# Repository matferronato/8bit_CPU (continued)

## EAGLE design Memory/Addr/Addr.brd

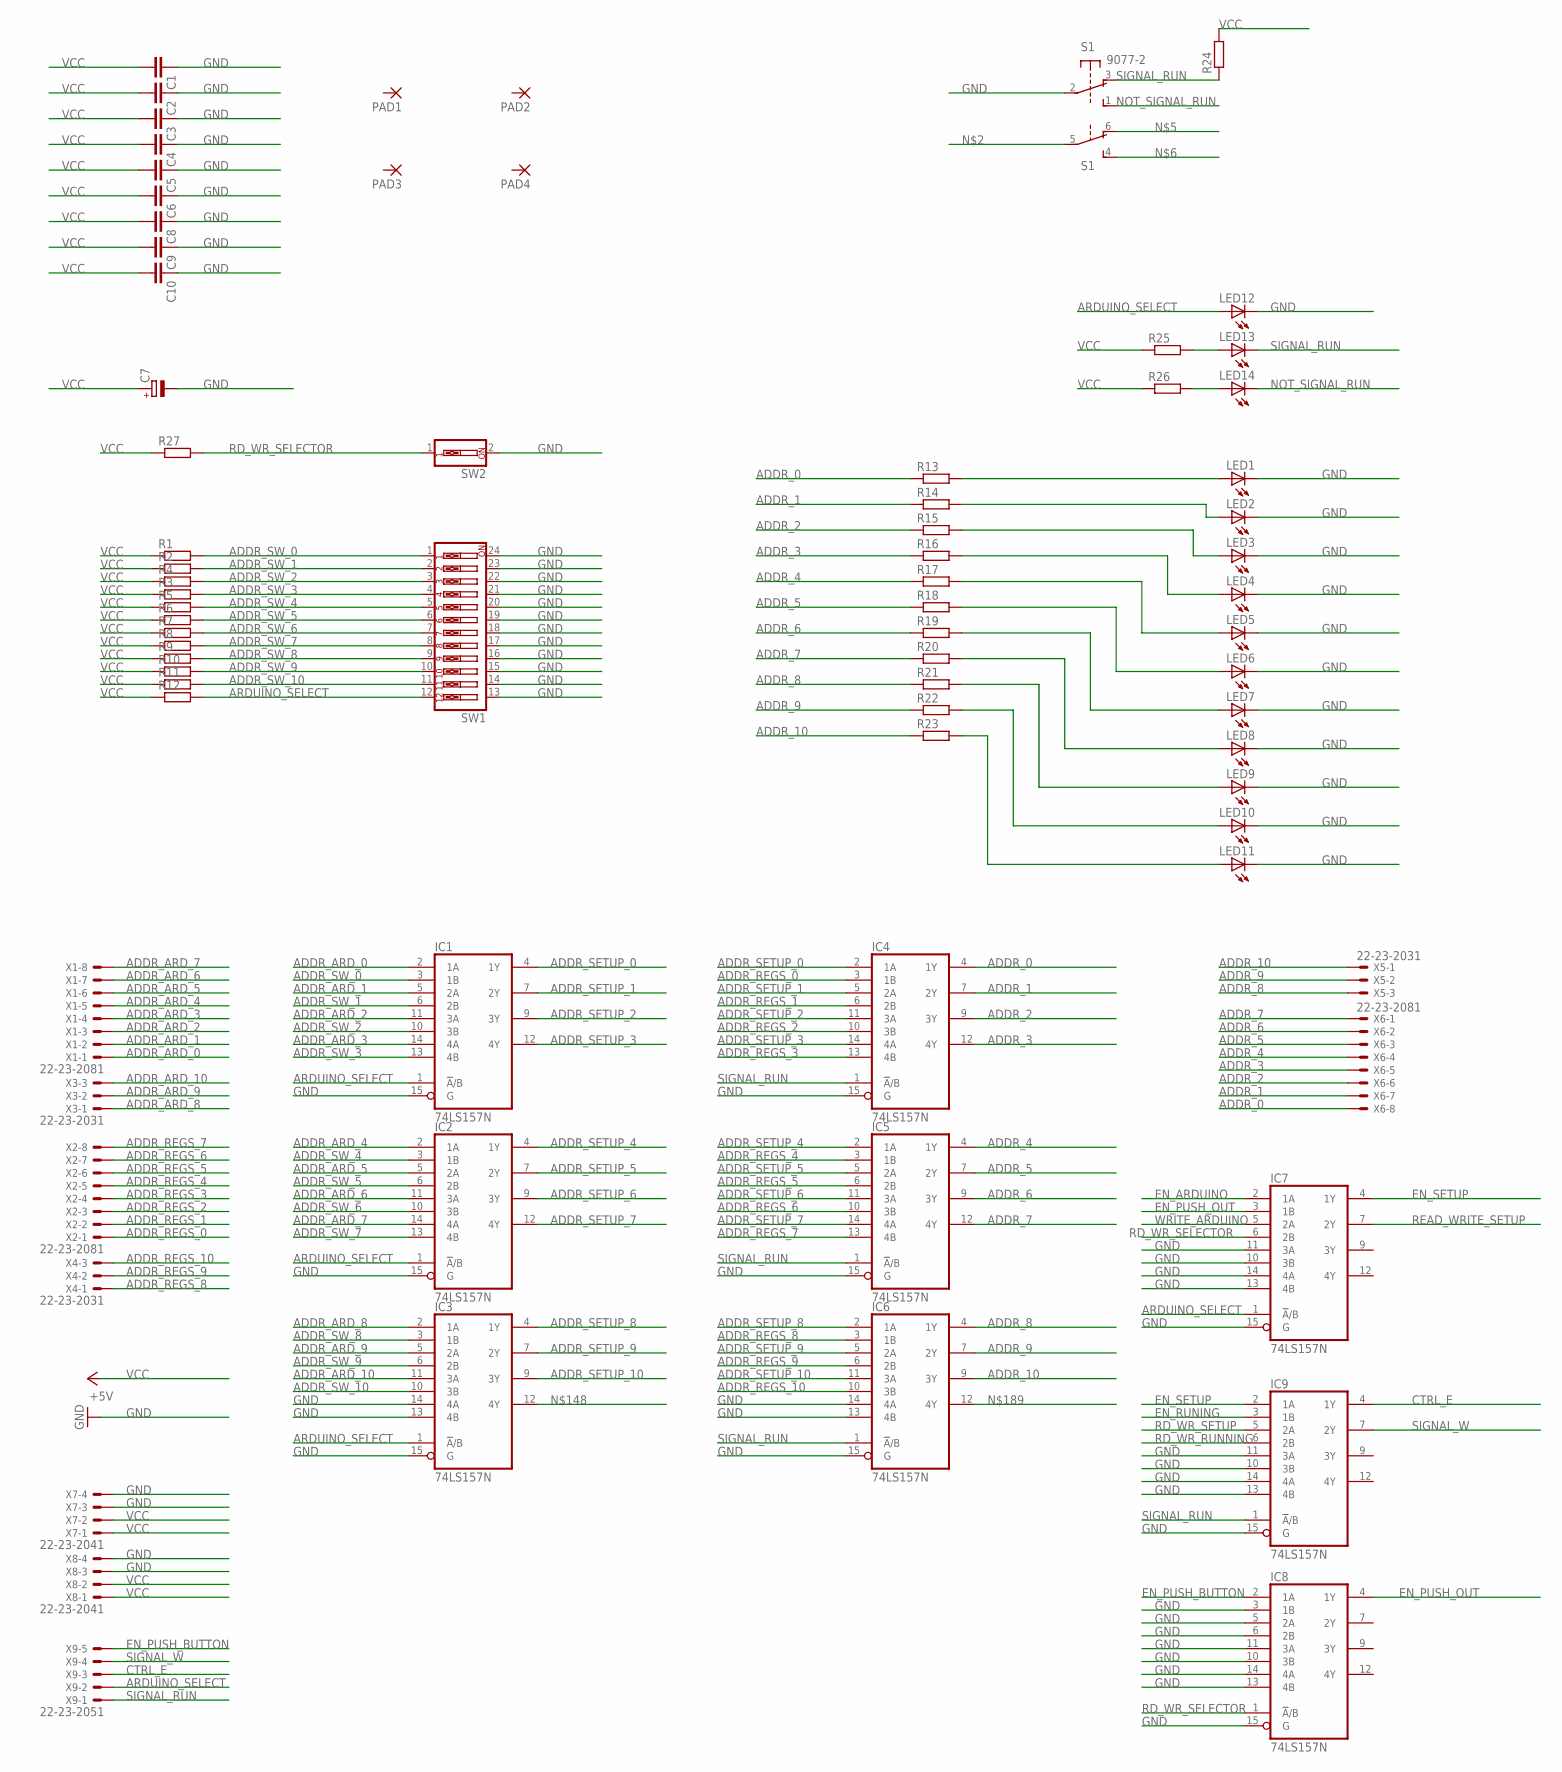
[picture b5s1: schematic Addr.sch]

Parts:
C1, C2, C3, C4, C5, C6, C8, C9, C10: C-EU025-025X050; C025-025X050
C7: CPOL-EUE2.5-6; E2,5-6
IC1, IC2, IC3, IC4, IC5, IC6, IC7, IC8, IC9: 74LS157N; DIL16
LED1, LED2, LED3, LED4, LED5, LED6, LED7, LED8, LED9, LED10, LED11, LED12, LED13, LED14: LED5MM
PAD1, PAD2, PAD3, PAD4: 3,17/1,3
R1, R2, R3, R4, R5, R6, R7, R8, R9, R10, R11, R12, R13, R14, R15, R16, R17, R18, R19, R20, R21, R22, R23, R24, R25, R26, R27: R0207/10; 0207/10
S1: 9077-2
SW1: SW_DIP-12; EDG-12
SW2: SW_DIP-1; EDG-01
X1, X2, X6: 22-23-2081
X3, X4, X5: 22-23-2031
X7, X8: 22-23-2041
X9: 22-23-2051

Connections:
ADDR_0: IC4.4 (1Y), R13.1, X6.8
ADDR_1: IC4.7 (2Y), R14.1, X6.7
ADDR_2: IC4.9 (3Y), R15.1, X6.6
ADDR_3: IC4.12 (4Y), R16.1, X6.5
ADDR_4: IC5.4 (1Y), R17.1, X6.4
ADDR_5: IC5.7 (2Y), R18.1, X6.3
ADDR_6: IC5.9 (3Y), R19.1, X6.2
ADDR_7: IC5.12 (4Y), R20.1, X6.1
ADDR_8: IC6.4 (1Y), R21.1, X5.3
ADDR_9: IC6.7 (2Y), R22.1, X5.2
ADDR_10: IC6.9 (3Y), R23.1, X5.1
ADDR_ARD_0: IC1.2 (1A), X1.1
ADDR_ARD_1: IC1.5 (2A), X1.2
ADDR_ARD_2: IC1.11 (3A), X1.3
ADDR_ARD_3: IC1.14 (4A), X1.4
ADDR_ARD_4: IC2.2 (1A), X1.5
ADDR_ARD_5: IC2.5 (2A), X1.6
ADDR_ARD_6: IC2.11 (3A), X1.7
ADDR_ARD_7: IC2.14 (4A), X1.8
ADDR_ARD_8: IC3.2 (1A), X3.1
ADDR_ARD_9: IC3.5 (2A), X3.2
ADDR_ARD_10: IC3.11 (3A), X3.3
ADDR_REGS_0: IC4.3 (1B), X2.1
ADDR_REGS_1: IC4.6 (2B), X2.2
ADDR_REGS_2: IC4.10 (3B), X2.3
ADDR_REGS_3: IC4.13 (4B), X2.4
ADDR_REGS_4: IC5.3 (1B), X2.5
ADDR_REGS_5: IC5.6 (2B), X2.6
ADDR_REGS_6: IC5.10 (3B), X2.7
ADDR_REGS_7: IC5.13 (4B), X2.8
ADDR_REGS_8: IC6.3 (1B), X4.1
ADDR_REGS_9: IC6.6 (2B), X4.2
ADDR_REGS_10: IC6.10 (3B), X4.3
ADDR_SETUP_0: IC1.4 (1Y), IC4.2 (1A)
ADDR_SETUP_1: IC1.7 (2Y), IC4.5 (2A)
ADDR_SETUP_2: IC1.9 (3Y), IC4.11 (3A)
ADDR_SETUP_3: IC1.12 (4Y), IC4.14 (4A)
ADDR_SETUP_4: IC2.4 (1Y), IC5.2 (1A)
ADDR_SETUP_5: IC2.7 (2Y), IC5.5 (2A)
ADDR_SETUP_6: IC2.9 (3Y), IC5.11 (3A)
ADDR_SETUP_7: IC2.12 (4Y), IC5.14 (4A)
ADDR_SETUP_8: IC3.4 (1Y), IC6.2 (1A)
ADDR_SETUP_9: IC3.7 (2Y), IC6.5 (2A)
ADDR_SETUP_10: IC3.9 (3Y), IC6.11 (3A)
ADDR_SW_0: IC1.3 (1B), R1.2, SW1.1
ADDR_SW_1: IC1.6 (2B), R2.2, SW1.2
ADDR_SW_2: IC1.10 (3B), R4.2, SW1.3
ADDR_SW_3: IC1.13 (4B), R3.2, SW1.4
ADDR_SW_4: IC2.3 (1B), R5.2, SW1.5
ADDR_SW_5: IC2.6 (2B), R6.2, SW1.6
ADDR_SW_6: IC2.10 (3B), R7.2, SW1.7
ADDR_SW_7: IC2.13 (4B), R8.2, SW1.8
ADDR_SW_8: IC3.3 (1B), R9.2, SW1.9
ADDR_SW_9: IC3.6 (2B), R10.2, SW1.10
ADDR_SW_10: IC3.10 (3B), R11.2, SW1.11
ARDUINO_SELECT: IC1.1 (!A!/B), IC2.1 (!A!/B), IC3.1 (!A!/B), IC7.1 (!A!/B), LED12.A, R12.2, SW1.12, X9.2
CTRL_E: IC9.4 (1Y), X9.3
EN_ARDUINO: IC7.2 (1A)
EN_PUSH_BUTTON: IC8.2 (1A), X9.5
EN_PUSH_OUT: IC7.3 (1B), IC8.4 (1Y)
EN_RUNING: IC9.3 (1B)
EN_SETUP: IC7.4 (1Y), IC9.2 (1A)
GND: C1.1, C2.1, C3.1, C4.1, C5.1, C6.1, C7.-, C8.1, C9.1, C10.1, IC1.8 (GND), IC1.15 (G), IC2.8 (GND), IC2.15 (G), IC3.8 (GND), IC3.13 (4B), IC3.14 (4A), IC3.15 (G), IC4.8 (GND), IC4.15 (G), IC5.8 (GND), IC5.15 (G), IC6.8 (GND), IC6.13 (4B), IC6.14 (4A), IC6.15 (G), IC7.8 (GND), IC7.10 (3B), IC7.11 (3A), IC7.13 (4B), IC7.14 (4A), IC7.15 (G), IC8.3 (1B), IC8.5 (2A), IC8.6 (2B), IC8.8 (GND), IC8.10 (3B), IC8.11 (3A), IC8.13 (4B), IC8.14 (4A), IC8.15 (G), IC9.8 (GND), IC9.10 (3B), IC9.11 (3A), IC9.13 (4B), IC9.14 (4A), IC9.15 (G), LED1.K (C), LED2.K (C), LED3.K (C), LED4.K (C), LED5.K (C), LED6.K (C), LED7.K (C), LED8.K (C), LED9.K (C), LED10.K (C), LED11.K (C), LED12.K (C), S1.2, SW1.13, SW1.14, SW1.15, SW1.16, SW1.17, SW1.18, SW1.19, SW1.20, SW1.21, SW1.22, SW1.23, SW1.24, SW2.2, X7.3, X7.4, X8.3, X8.4
unnamed: LED13.A, R25.2
unnamed: LED14.A, R26.2
unnamed: LED1.A, R13.2
unnamed: LED2.A, R14.2
unnamed: LED3.A, R15.2
unnamed: LED4.A, R16.2
unnamed: LED5.A, R17.2
unnamed: LED6.A, R18.2
unnamed: LED7.A, R19.2
unnamed: LED8.A, R20.2
unnamed: LED9.A, R21.2
unnamed: LED10.A, R22.2
unnamed: LED11.A, R23.2
NOT_SIGNAL_RUN: LED14.K (C), S1.1 (S)
RD_WR_RUNNING: IC9.6 (2B)
RD_WR_SELECTOR: IC7.6 (2B), IC8.1 (!A!/B), R27.2, SW2.1
RD_WR_SETUP: IC9.5 (2A)
READ_WRITE_SETUP: IC7.7 (2Y)
SIGNAL_RUN: IC4.1 (!A!/B), IC5.1 (!A!/B), IC6.1 (!A!/B), IC9.1 (!A!/B), LED13.K (C), R24.1, S1.3 (O), X9.1
SIGNAL_W: IC9.7 (2Y), X9.4
VCC: C1.2, C2.2, C3.2, C4.2, C5.2, C6.2, C7.+, C8.2, C9.2, C10.2, IC1.16 (VCC), IC2.16 (VCC), IC3.16 (VCC), IC4.16 (VCC), IC5.16 (VCC), IC6.16 (VCC), IC7.16 (VCC), IC8.16 (VCC), IC9.16 (VCC), R1.1, R2.1, R3.1, R4.1, R5.1, R6.1, R7.1, R8.1, R9.1, R10.1, R11.1, R12.1, R24.2, R25.1, R26.1, R27.1, X7.1, X7.2, X8.1, X8.2
WRITE_ARDUINO: IC7.5 (2A)

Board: 2 copper layers, 76 parts (0 on the bottom side), 79 nets, no tracks yet.

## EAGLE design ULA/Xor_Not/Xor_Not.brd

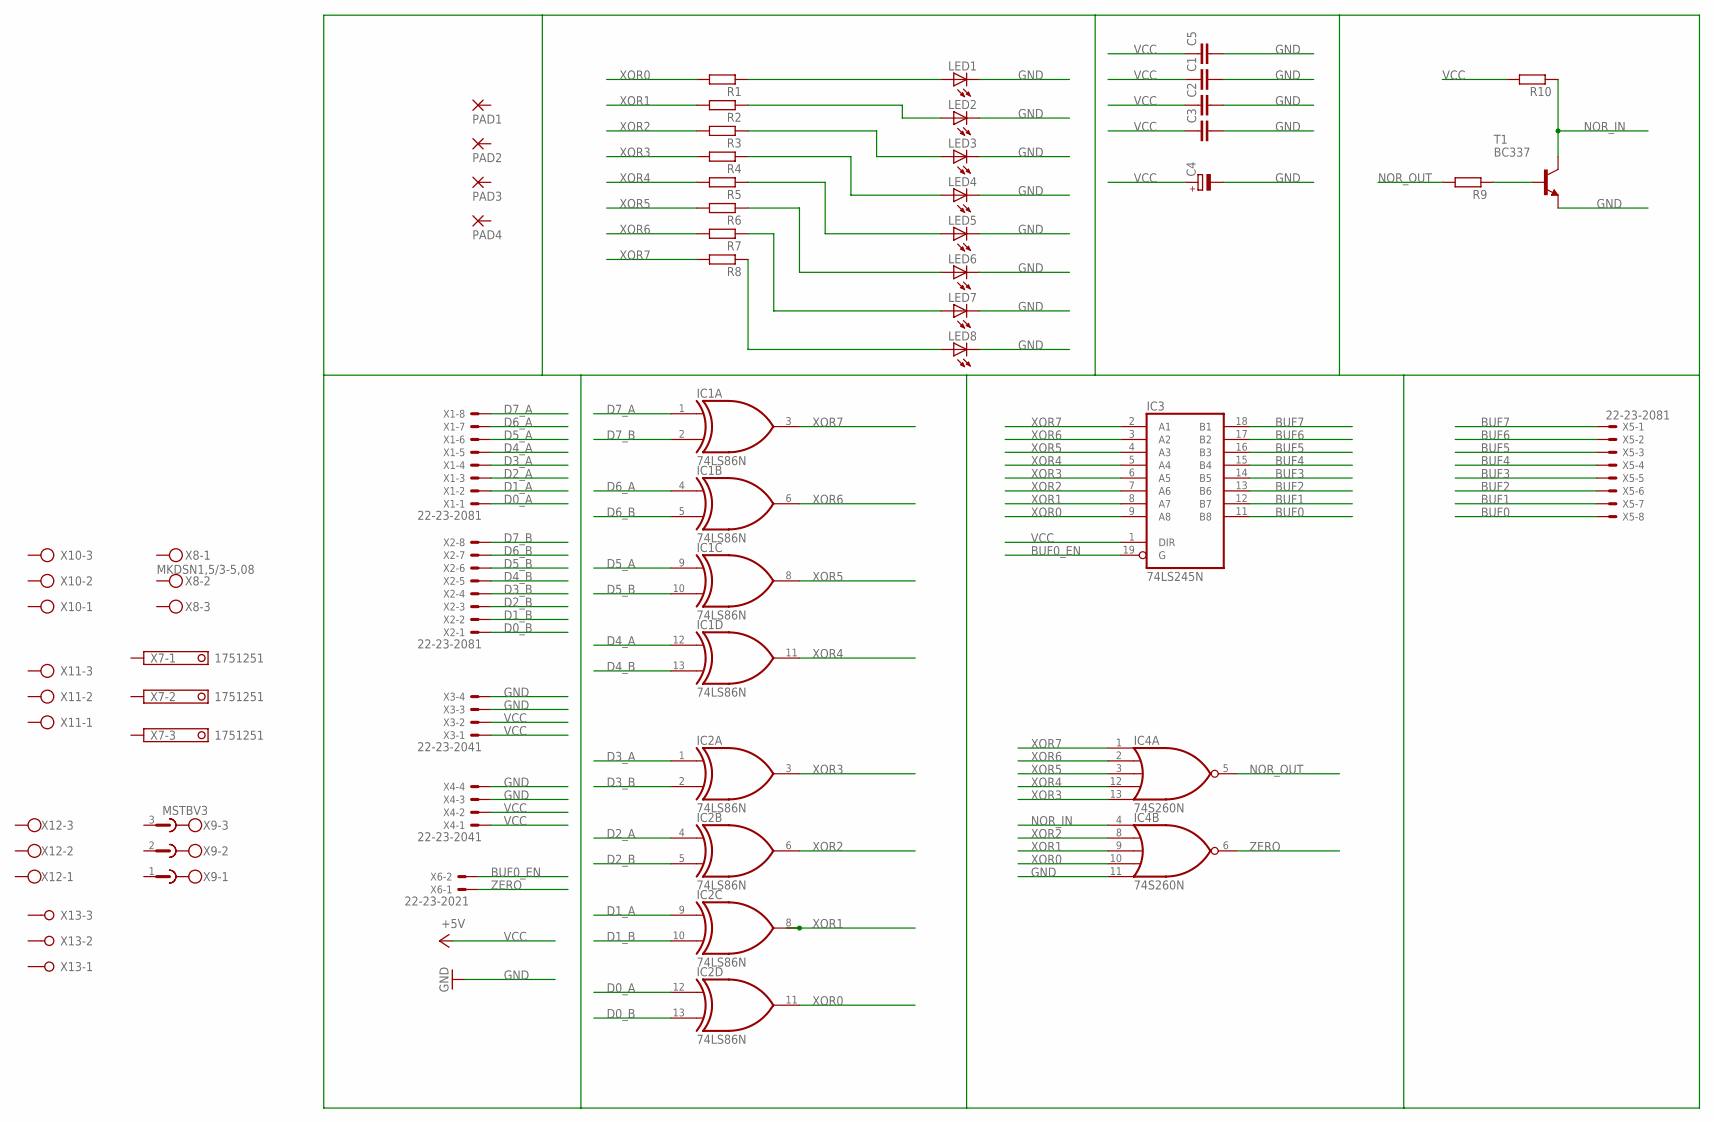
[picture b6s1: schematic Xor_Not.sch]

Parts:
C1, C2, C3, C5: C-EU025-025X050; C025-025X050
C4: CPOL-EUE2.5-6; E2,5-6
IC1, IC2: 74LS86N; DIL14
IC3: 74LS245N; DIL20
IC4: 74S260N; DIL14
LED1, LED2, LED3, LED4, LED5, LED6, LED7, LED8: LED5MM
PAD1, PAD2, PAD3, PAD4: 3,17/1,3
R1, R2, R3, R4, R5, R6, R7, R8, R9, R10: R0207/10; 0207/10
T1: BC337; TO92
X1, X2, X5: 22-23-2081
X3, X4: 22-23-2041
X6: 22-23-2021
X7: 1751251
X8: MKDSN1,5/3-5,08
X9: MSTBV3
X10: AK300/3
X11: AK500/3-H
X12: W237-103
X13: W237-03P; W237-133

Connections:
BUF0: IC3.11 (B8), X5.8
BUF0_EN: IC3.19 (G), X6.2
BUF1: IC3.12 (B7), X5.7
BUF2: IC3.13 (B6), X5.6
BUF3: IC3.14 (B5), X5.5
BUF4: IC3.15 (B4), X5.4
BUF5: IC3.16 (B3), X5.3
BUF6: IC3.17 (B2), X5.2
BUF7: IC3.18 (B1), X5.1
D0_A: IC2.12 (I0), X1.1
D0_B: IC2.13 (I1), X2.1
D1_A: IC2.9 (I0), X1.2
D1_B: IC2.10 (I1), X2.2
D2_A: IC2.4 (I0), X1.3
D2_B: IC2.5 (I1), X2.3
D3_A: IC2.1 (I0), X1.4
D3_B: IC2.2 (I1), X2.4
D4_A: IC1.12 (I0), X1.5
D4_B: IC1.13 (I1), X2.5
D5_A: IC1.9 (I0), X1.6
D5_B: IC1.10 (I1), X2.6
D6_A: IC1.4 (I0), X1.7
D6_B: IC1.5 (I1), X2.7
D7_A: IC1.1 (I0), X1.8
D7_B: IC1.2 (I1), X2.8
GND: C1.2, C2.2, C3.2, C4.-, C5.2, IC1.7 (GND), IC2.7 (GND), IC3.10 (GND), IC4.7 (GND), IC4.11 (I4), LED1.K (C), LED2.K (C), LED3.K (C), LED4.K (C), LED5.K (C), LED6.K (C), LED7.K (C), LED8.K (C), T1.1 (E), X3.3, X3.4, X4.3, X4.4
unnamed: R9.1, T1.2 (B)
unnamed: LED1.A, R1.1
unnamed: LED2.A, R2.1
unnamed: LED3.A, R3.1
unnamed: LED4.A, R4.1
unnamed: LED5.A, R5.1
unnamed: LED6.A, R6.1
unnamed: LED7.A, R7.1
unnamed: LED8.A, R8.1
NOR_IN: IC4.4 (I0), R10.1, T1.3 (C)
NOR_OUT: IC4.5 (O), R9.2
VCC: C1.1, C2.1, C3.1, C4.+, C5.1, IC1.14 (VCC), IC2.14 (VCC), IC3.1 (DIR), IC3.20 (VCC), IC4.14 (VCC), R10.2, X3.1, X3.2, X4.1, X4.2
XOR0: IC2.11 (O), IC3.9 (A8), IC4.10 (I3), R1.2
XOR1: IC2.8 (O), IC3.8 (A7), IC4.9 (I2), R2.2
XOR2: IC2.6 (O), IC3.7 (A6), IC4.8 (I1), R3.2
XOR3: IC2.3 (O), IC3.6 (A5), IC4.13 (I4), R4.2
XOR4: IC1.11 (O), IC3.5 (A4), IC4.12 (I3), R5.2
XOR5: IC1.8 (O), IC3.4 (A3), IC4.3 (I2), R6.2
XOR6: IC1.6 (O), IC3.3 (A2), IC4.2 (I1), R7.2
XOR7: IC1.3 (O), IC3.2 (A1), IC4.1 (I0), R8.2
ZERO: IC4.6 (O), X6.1

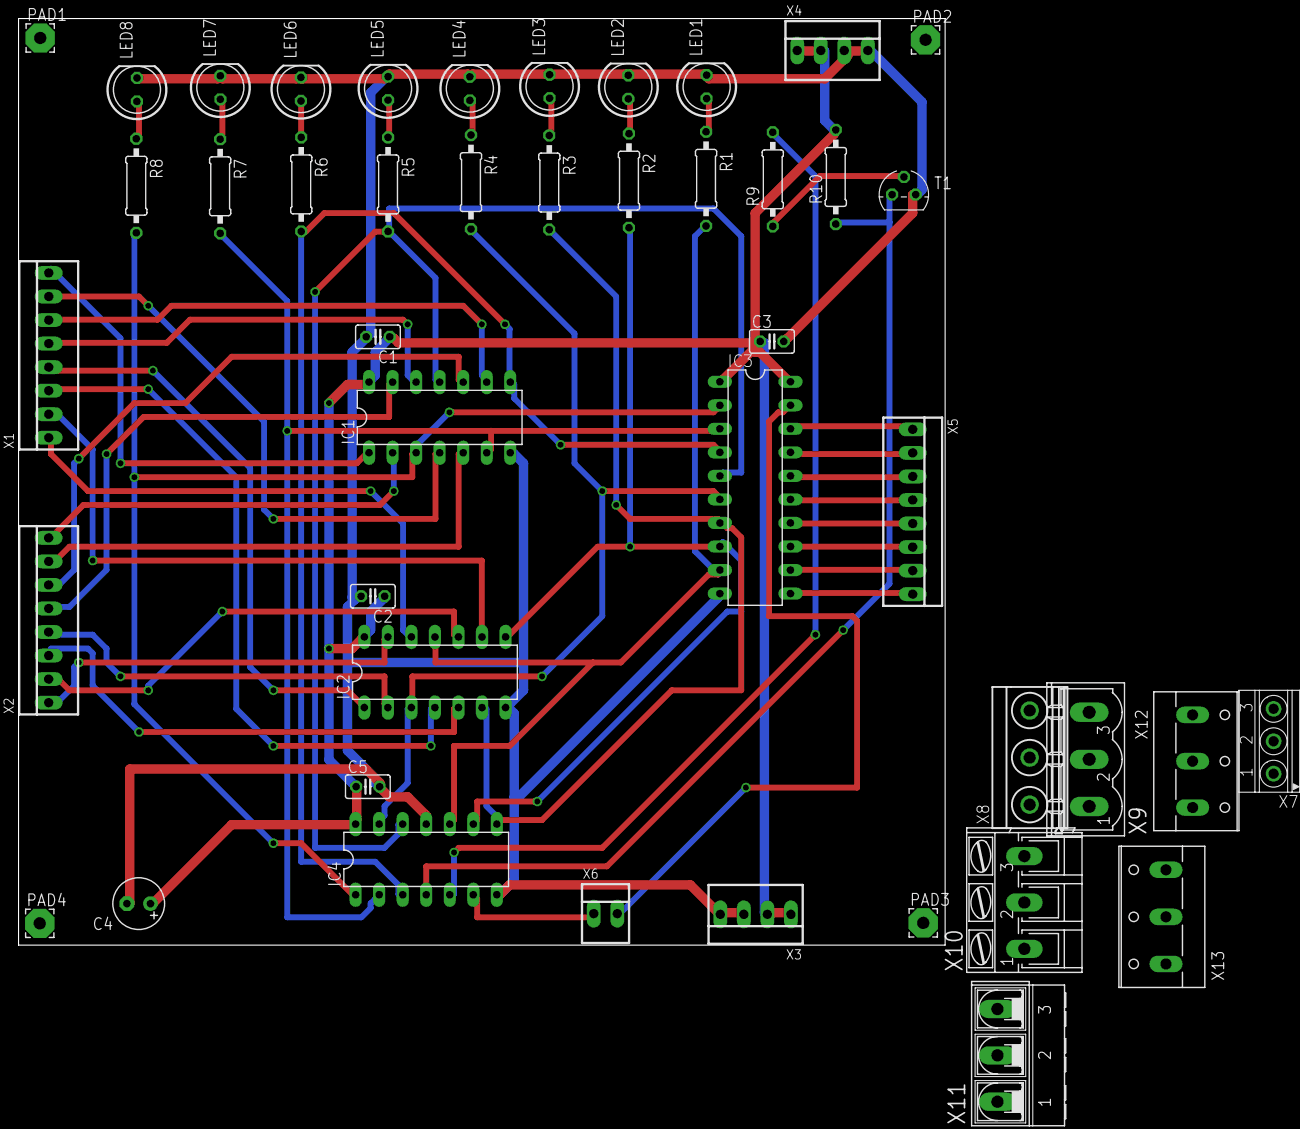
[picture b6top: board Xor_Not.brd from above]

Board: 2 copper layers, 100.0 x 100.0 mm, 45 parts (0 on the bottom side), 47 nets.

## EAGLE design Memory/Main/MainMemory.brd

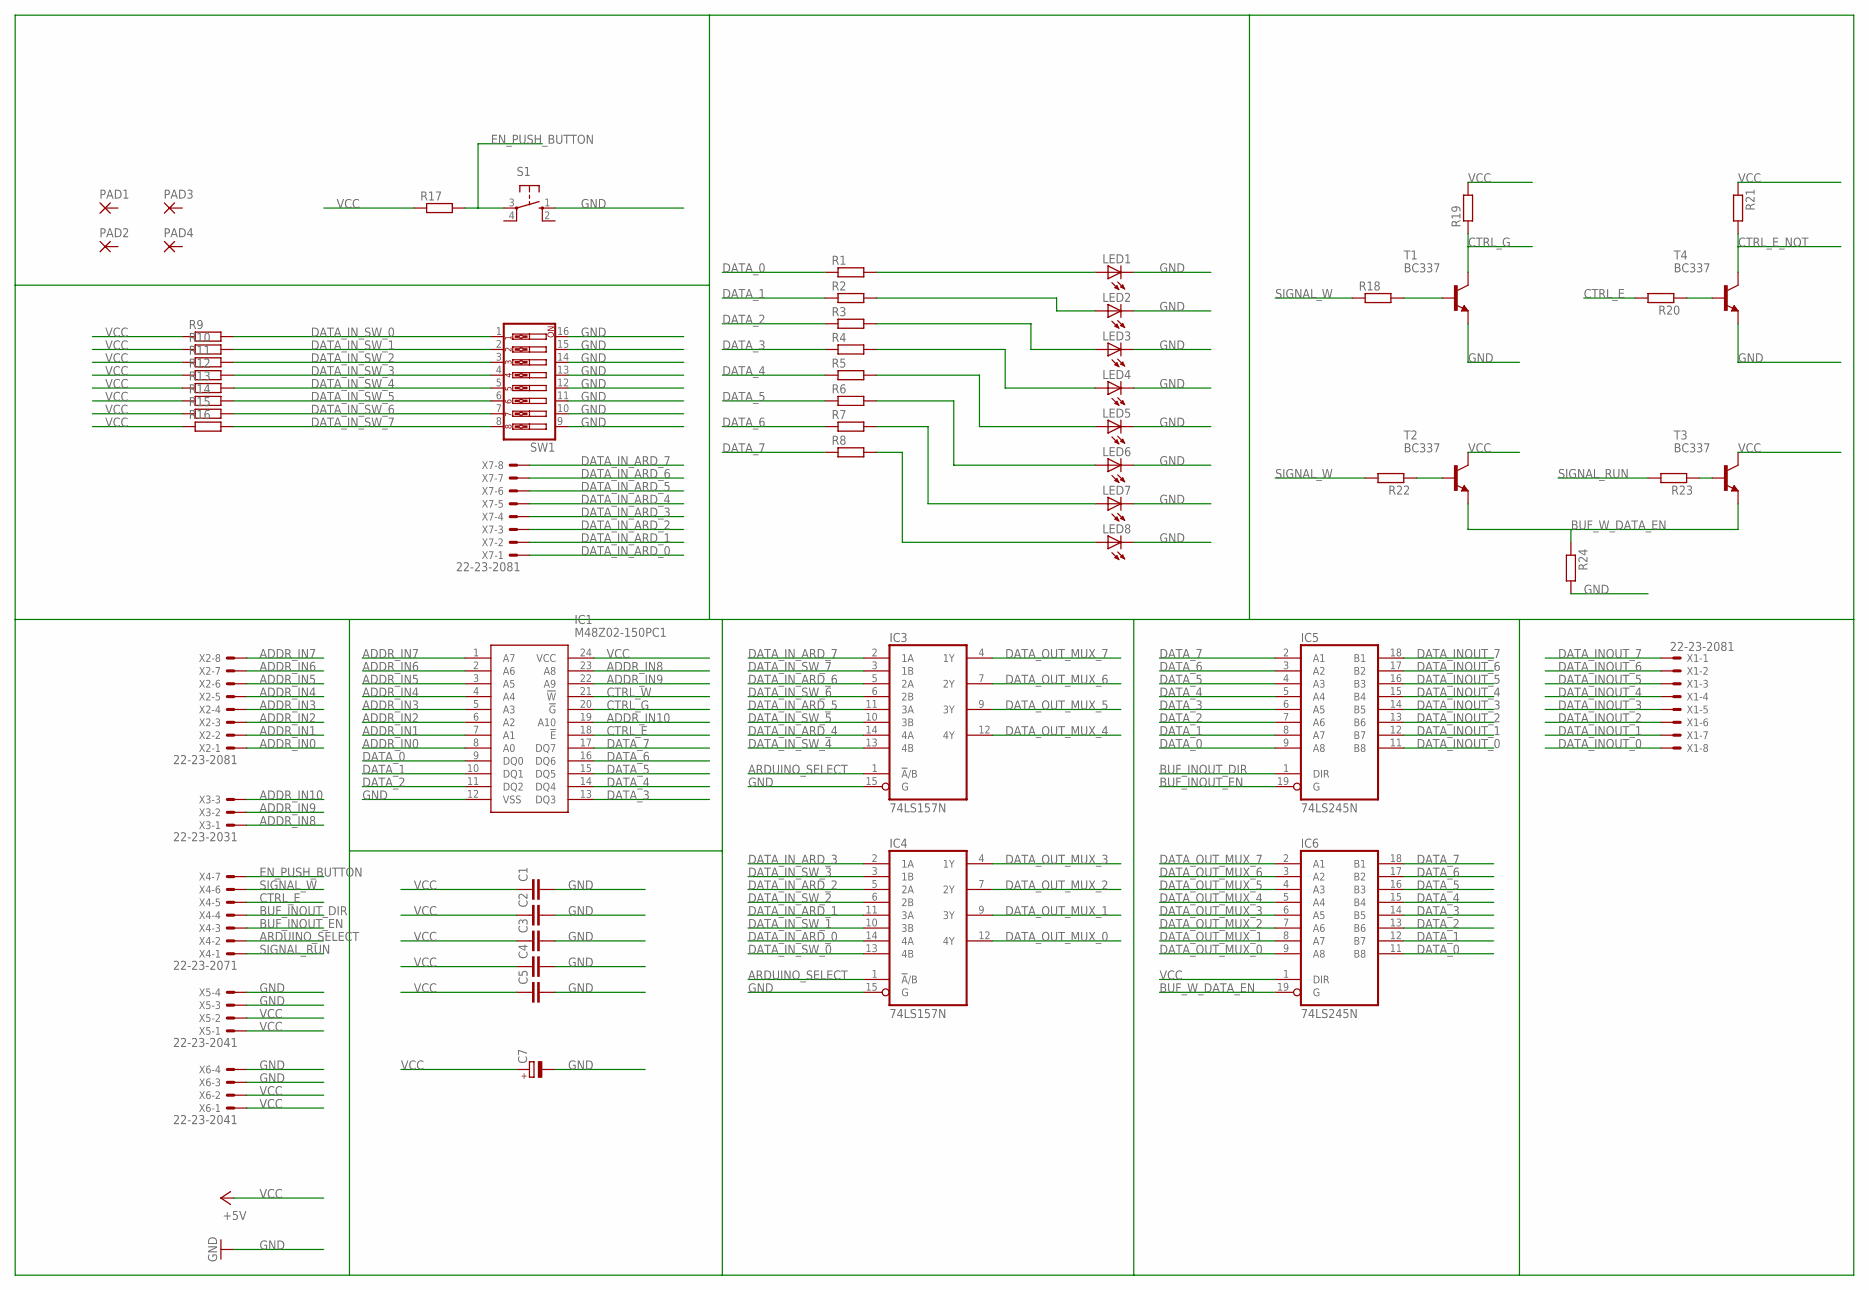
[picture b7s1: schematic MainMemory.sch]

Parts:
C1, C2, C3, C4, C5: C-EU025-025X050; C025-025X050
C7: CPOL-EUE2.5-6; E2,5-6
IC1: M48Z02-150PC1; DIP1562W53P279L3454H965Q24N
IC3, IC4: 74LS157N; DIL16
IC5, IC6: 74LS245N; DIL20
LED1, LED2, LED3, LED4, LED5, LED6, LED7, LED8: LED5MM
PAD1, PAD2, PAD3, PAD4: 3,17/1,3
R1, R2, R3, R4, R5, R6, R7, R8, R9, R10, R11, R12, R13, R14, R15, R16, R17, R18, R19, R20, R21, R22, R23, R24: R0207/10; 0207/10
S1: 10-XX; B3F-10XX
SW1: SW_DIP-8; EDG-08
T1, T2, T3, T4: BC337; TO92
X1, X2, X7: 22-23-2081
X3: 22-23-2031
X4: 22-23-2071
X5, X6: 22-23-2041

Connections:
ADDR_IN0: IC1.8 (A0), X2.1
ADDR_IN1: IC1.7 (A1), X2.2
ADDR_IN2: IC1.6 (A2), X2.3
ADDR_IN3: IC1.5 (A3), X2.4
ADDR_IN4: IC1.4 (A4), X2.5
ADDR_IN5: IC1.3 (A5), X2.6
ADDR_IN6: IC1.2 (A6), X2.7
ADDR_IN7: IC1.1 (A7), X2.8
ADDR_IN8: IC1.23 (A8), X3.1
ADDR_IN9: IC1.22 (A9), X3.2
ADDR_IN10: IC1.19 (A10), X3.3
ARDUINO_SELECT: IC3.1 (!A!/B), IC4.1 (!A!/B), X4.2
BUF_INOUT_DIR: IC5.1 (DIR), X4.4
BUF_INOUT_EN: IC5.19 (G), X4.3
BUF_W_DATA_EN: IC6.19 (G), R24.1, T2.1 (E), T3.1 (E)
CTRL_E: IC1.18 (!E), R20.2, X4.5
CTRL_E_NOT: R21.2, T4.3 (C)
CTRL_G: IC1.20 (!G), R19.1, T1.3 (C)
CTRL_W: IC1.21 (!W)
DATA_0: IC1.9 (DQ0), IC5.9 (A8), IC6.11 (B8), R1.1
DATA_1: IC1.10 (DQ1), IC5.8 (A7), IC6.12 (B7), R2.1
DATA_2: IC1.11 (DQ2), IC5.7 (A6), IC6.13 (B6), R3.1
DATA_3: IC1.13 (DQ3), IC5.6 (A5), IC6.14 (B5), R4.1
DATA_4: IC1.14 (DQ4), IC5.5 (A4), IC6.15 (B4), R5.1
DATA_5: IC1.15 (DQ5), IC5.4 (A3), IC6.16 (B3), R6.1
DATA_6: IC1.16 (DQ6), IC5.3 (A2), IC6.17 (B2), R7.1
DATA_7: IC1.17 (DQ7), IC5.2 (A1), IC6.18 (B1), R8.1
DATA_INOUT_0: IC5.11 (B8), X1.8
DATA_INOUT_1: IC5.12 (B7), X1.7
DATA_INOUT_2: IC5.13 (B6), X1.6
DATA_INOUT_3: IC5.14 (B5), X1.5
DATA_INOUT_4: IC5.15 (B4), X1.4
DATA_INOUT_5: IC5.16 (B3), X1.3
DATA_INOUT_6: IC5.17 (B2), X1.2
DATA_INOUT_7: IC5.18 (B1), X1.1
DATA_IN_ARD_0: IC4.14 (4A), X7.1
DATA_IN_ARD_1: IC4.11 (3A), X7.2
DATA_IN_ARD_2: IC4.5 (2A), X7.3
DATA_IN_ARD_3: IC4.2 (1A), X7.4
DATA_IN_ARD_4: IC3.14 (4A), X7.5
DATA_IN_ARD_5: IC3.11 (3A), X7.6
DATA_IN_ARD_6: IC3.5 (2A), X7.7
DATA_IN_ARD_7: IC3.2 (1A), X7.8
DATA_IN_SW_0: IC4.13 (4B), R9.2, SW1.1
DATA_IN_SW_1: IC4.10 (3B), R10.2, SW1.2
DATA_IN_SW_2: IC4.6 (2B), R11.2, SW1.3
DATA_IN_SW_3: IC4.3 (1B), R12.2, SW1.4
DATA_IN_SW_4: IC3.13 (4B), R13.2, SW1.5
DATA_IN_SW_5: IC3.10 (3B), R14.2, SW1.6
DATA_IN_SW_6: IC3.6 (2B), R15.2, SW1.7
DATA_IN_SW_7: IC3.3 (1B), R16.2, SW1.8
DATA_OUT_MUX_0: IC4.12 (4Y), IC6.9 (A8)
DATA_OUT_MUX_1: IC4.9 (3Y), IC6.8 (A7)
DATA_OUT_MUX_2: IC4.7 (2Y), IC6.7 (A6)
DATA_OUT_MUX_3: IC4.4 (1Y), IC6.6 (A5)
DATA_OUT_MUX_4: IC3.12 (4Y), IC6.5 (A4)
DATA_OUT_MUX_5: IC3.9 (3Y), IC6.4 (A3)
DATA_OUT_MUX_6: IC3.7 (2Y), IC6.3 (A2)
DATA_OUT_MUX_7: IC3.4 (1Y), IC6.2 (A1)
EN_PUSH_BUTTON: R17.2, S1.3, X4.7
GND: C1.2, C2.2, C3.2, C4.2, C5.2, C7.-, IC1.12 (VSS), IC3.8 (GND), IC3.15 (G), IC4.8 (GND), IC4.15 (G), IC5.10 (GND), IC6.10 (GND), LED1.K (C), LED2.K (C), LED3.K (C), LED4.K (C), LED5.K (C), LED6.K (C), LED7.K (C), LED8.K (C), R24.2, S1.1 (S), SW1.9, SW1.10, SW1.11, SW1.12, SW1.13, SW1.14, SW1.15, SW1.16, T1.1 (E), T4.1 (E), X5.3, X5.4, X6.3, X6.4
unnamed: LED1.A, R1.2
unnamed: LED2.A, R2.2
unnamed: LED3.A, R3.2
unnamed: LED4.A, R4.2
unnamed: LED5.A, R5.2
unnamed: LED6.A, R6.2
unnamed: LED7.A, R7.2
unnamed: LED8.A, R8.2
unnamed: R23.1, T3.2 (B)
unnamed: R22.1, T2.2 (B)
unnamed: R18.2, T1.2 (B)
unnamed: R20.1, T4.2 (B)
SIGNAL_RUN: R23.2, X4.1
SIGNAL_W: R18.1, R22.2, X4.6
VCC: C1.1, C2.1, C3.1, C4.1, C5.1, C7.+, IC1.24 (VCC), IC3.16 (VCC), IC4.16 (VCC), IC5.20 (VCC), IC6.1 (DIR), IC6.20 (VCC), R9.1, R10.1, R11.1, R12.1, R13.1, R14.1, R15.1, R16.1, R17.1, R19.2, R21.1, T2.3 (C), T3.3 (C), X5.1, X5.2, X6.1, X6.2

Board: 2 copper layers, 60 parts (0 on the bottom side), 75 nets, no tracks yet.
